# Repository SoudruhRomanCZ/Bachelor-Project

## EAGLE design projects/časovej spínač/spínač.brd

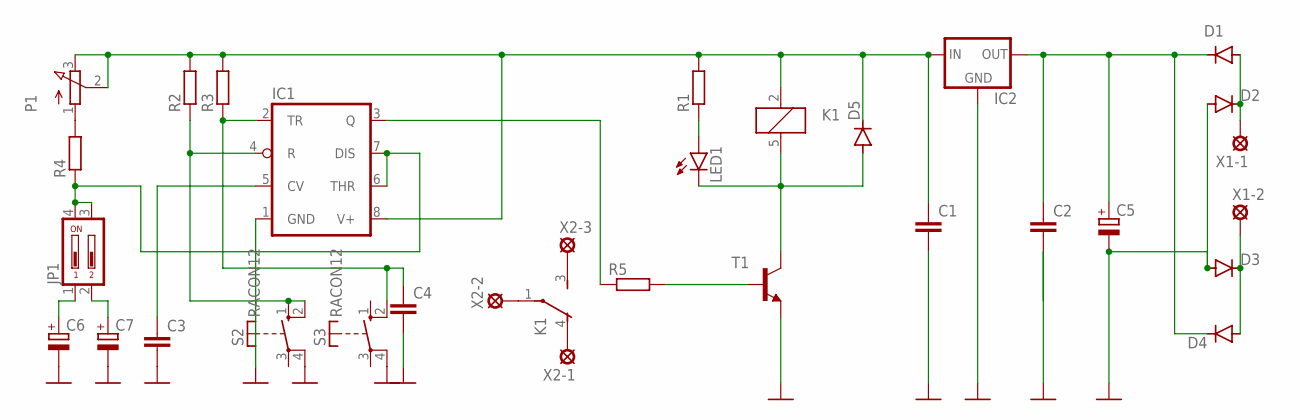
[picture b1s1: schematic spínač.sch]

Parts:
C1, C2, C3, C4: C-EU025-030X050; C025-030X050
C5, C6, C7: CPOL-EUB45181B; B45181B
D1, D2, D3, D4, D5: 1N4004; DO41-10
IC1: LM555N; DIL08
IC2: 78XXL
JP1: 219-02J; CTS-219-02J
K1: AZ8-FORM-C; AZ8
LED1: TLLR4400; LED3MM
P1: 3RP/1610N
R1, R2, R3, R4, R5: R-EU_0207/10; 0207/10
S2, S3: RACON12
T1: 2N3565; TO92
X1-1, X1-2, X2-1, X2-2, X2-3: SE14

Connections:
GND: C1.2, C2.2, C3.2, C4.2, C5.-, C6.-, C7.-, D2.A, D3.A, IC1.1 (GND), IC2.GND, S2.4, S3.4, T1.3 (E)
unnamed: D3.C, D4.A, X1-2.MP
unnamed: C2.1, C5.+, D1.C, D4.C, IC2.OUT
unnamed: C1.1, D5.C, IC1.8 (V+), IC2.IN, K1.2 (1), P1.2 (S), P1.3 (E), R1.2, R2.2, R3.2
unnamed: D1.A, D2.C, X1-1.MP
unnamed: D5.A, K1.5 (2), LED1.K (C), T1.1 (C)
unnamed: LED1.A, R1.1
unnamed: R5.2, T1.2 (B)
unnamed: IC1.3 (Q), R5.1
unnamed: C4.1, IC1.2 (TR), R3.1, S3.2 (S)
unnamed: IC1.4 (R), R2.1, S2.1 (S), S2.2 (S)
unnamed: C6.+, JP1.1
unnamed: C7.+, JP1.2
unnamed: IC1.6 (THR), IC1.7 (DIS), JP1.3, JP1.4, R4.1
unnamed: P1.1 (A), R4.2
unnamed: C3.1, IC1.5 (CV)
unnamed: K1.3 (S), X2-3.MP
unnamed: K1.1, X2-2.MP
unnamed: K1.4 (O), X2-1.MP

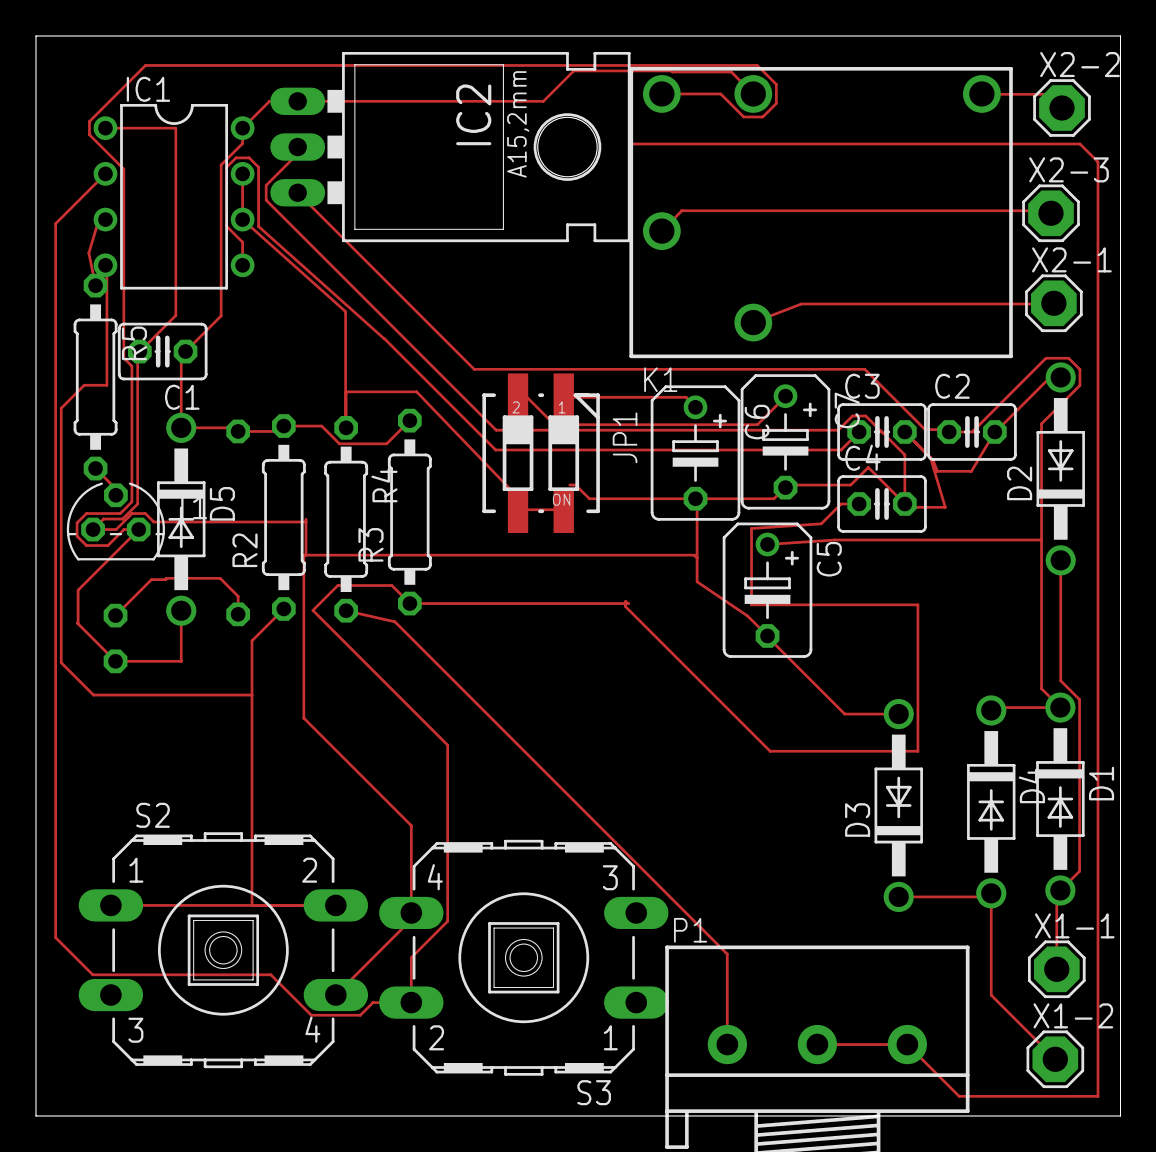
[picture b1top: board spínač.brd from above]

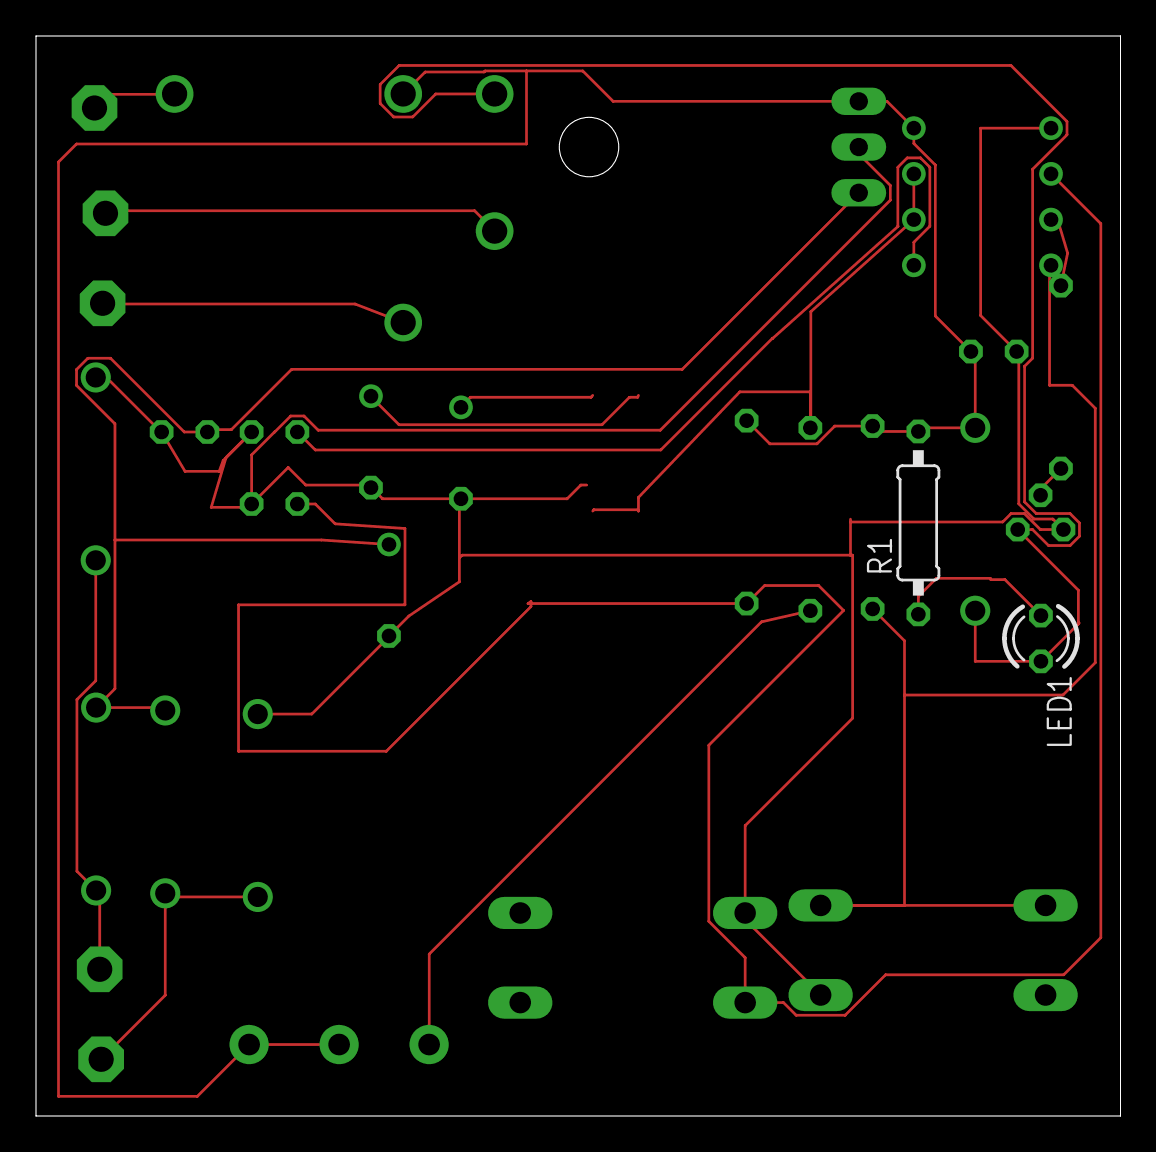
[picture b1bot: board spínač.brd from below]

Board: 2 copper layers, 60.2 x 60.0 mm, 31 parts (2 on the bottom side), 19 nets.

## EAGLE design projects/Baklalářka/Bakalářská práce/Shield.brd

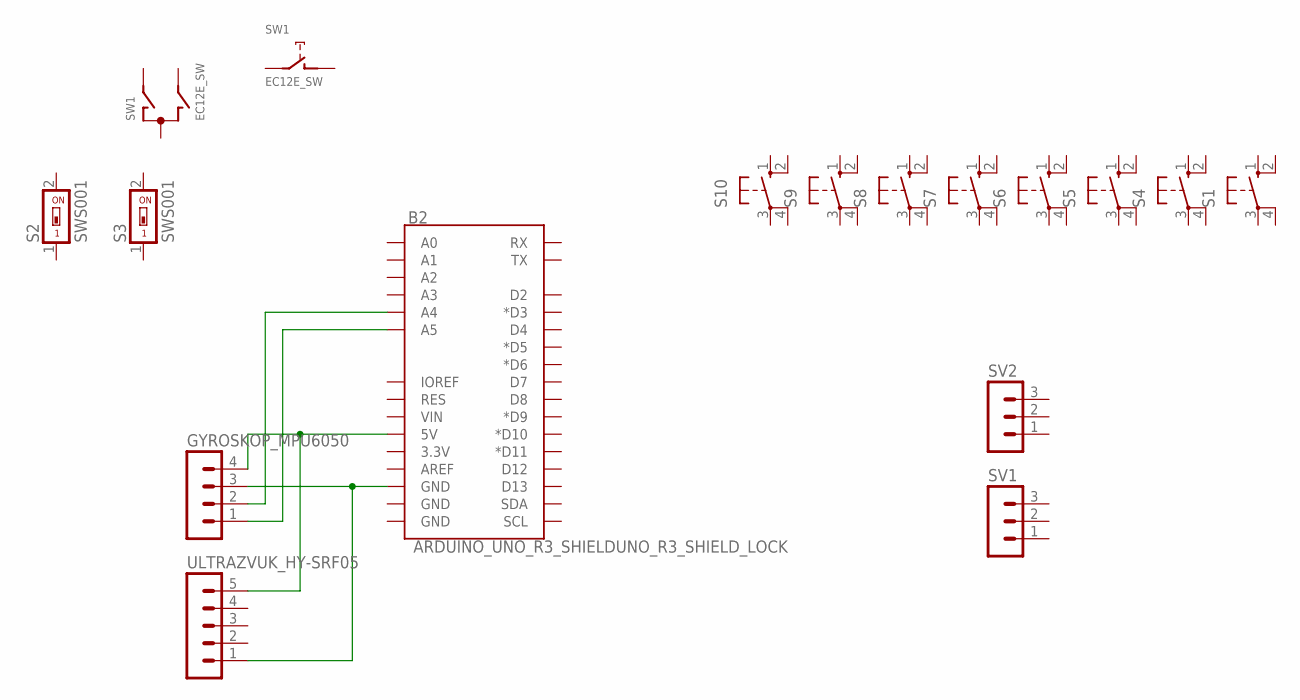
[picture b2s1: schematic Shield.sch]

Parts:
B2: ARDUINO_UNO_R3_SHIELDUNO_R3_SHIELD_LOCK; UNO_R3_SHIELD_LOCK
GYROSKOP_MPU6050: MA04-1
S1, S4, S5, S6, S7, S8, S9, S10: 10-XX; B3F-10XX
S2, S3: SWS001; SMS-001
SV1, SV2: MA03-1
SW1: EC12E_SW; ALPS_EC12E_SW
ULTRAZVUK_HY-SRF05: MA05-1

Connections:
unnamed: B2.A4, GYROSKOP_MPU6050.2
unnamed: B2.A5, GYROSKOP_MPU6050.1
unnamed: B2.5V, GYROSKOP_MPU6050.4, ULTRAZVUK_HY-SRF05.5
unnamed: B2.GND@2 (GND), GYROSKOP_MPU6050.3, ULTRAZVUK_HY-SRF05.1

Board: 2 copper layers, 16 parts (0 on the bottom side), 4 nets, no tracks yet.

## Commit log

2023-09-21 Create LICENSE
2023-09-21 added arduino template
2023-09-21 added Eagle data
2023-09-21 redefined bipolar switch
2023-09-24 added word file
2023-09-27 added gyroscope ultrasound and joystick code
2023-09-27 copied example codes into main.cpp
2023-10-04 4-10_update
2023-10-04 wifi receiver and trasmitter added
2023-11-03 rebranded mai.cpp file
2023-11-03 added case files and rebranded main.cpp

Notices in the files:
parts and their libraries:
SparkFun-Boards: Licensing: Creative Commons ShareAlike 4.0 International - https://creativecommons.org/licenses/by-sa/4.0
